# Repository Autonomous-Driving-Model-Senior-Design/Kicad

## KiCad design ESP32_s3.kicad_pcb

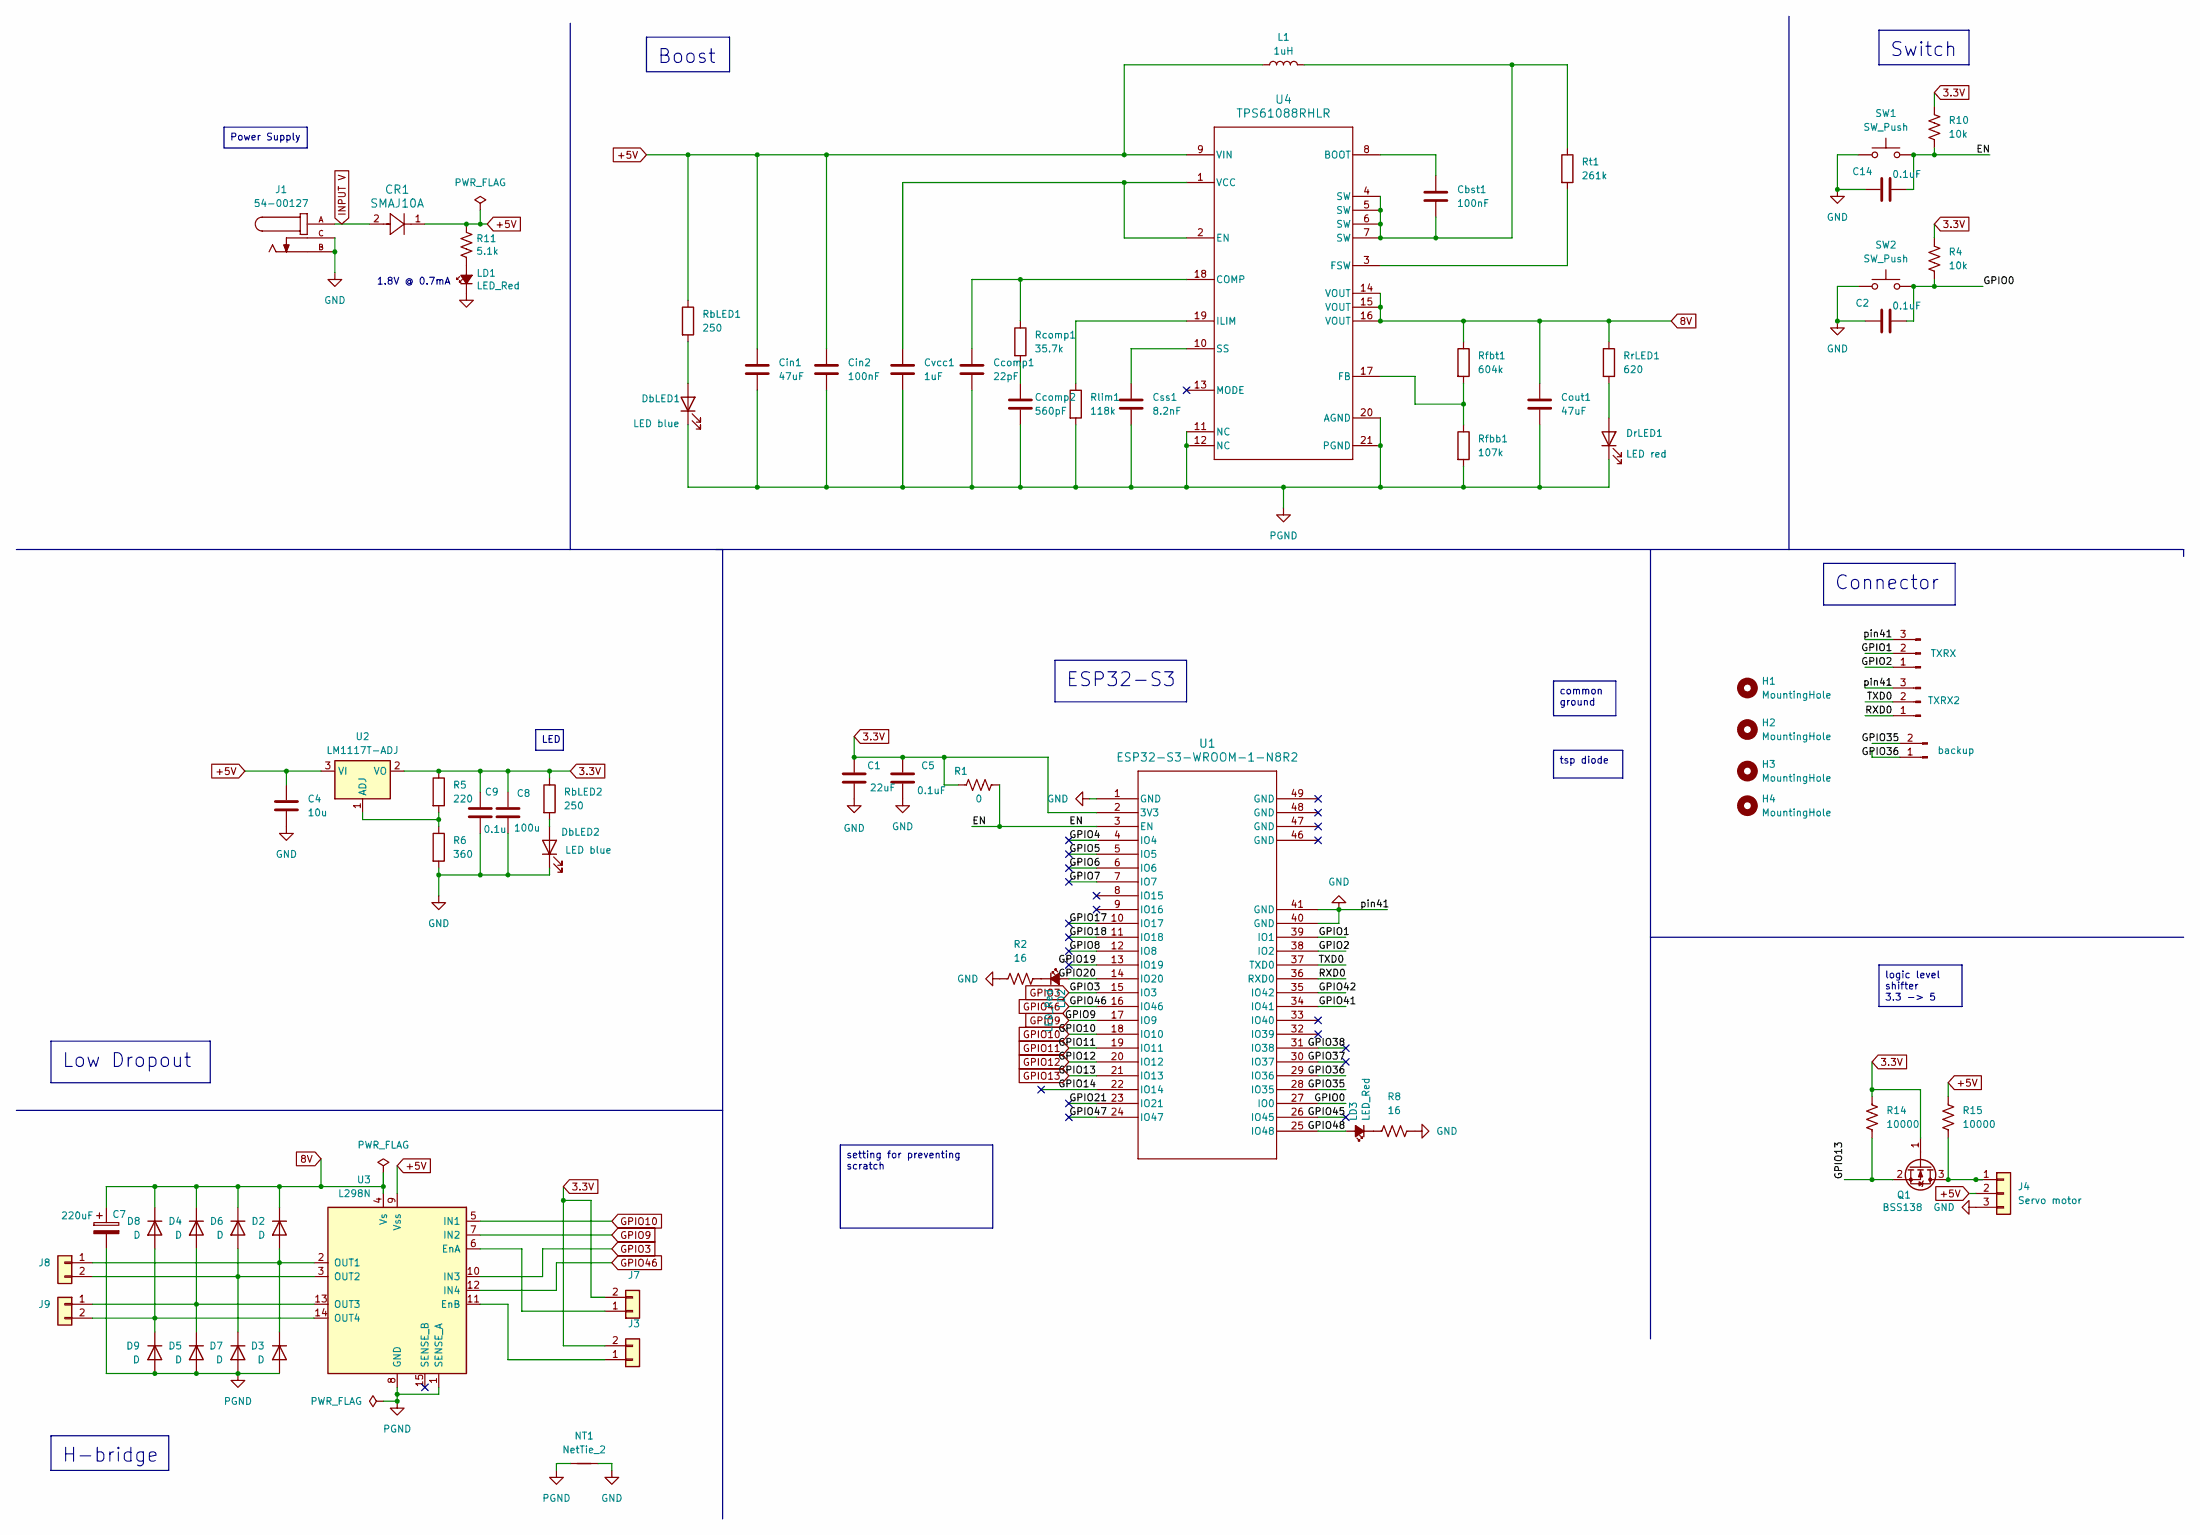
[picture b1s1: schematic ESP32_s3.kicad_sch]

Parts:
C1: 22uF; CAPC2012X135N
C2, C5, C14: 0.1uF; CAPC3316X140N
C4: 10u; CAPC230145_145N_KEM
C7: 220uF; CAPC3216X190N
C8: 100u; CAPC2012X145N
C9: 0.1u; CAPC2012X145N
CR1: SMAJ10A; SMASeries_LTF
Cbst1: 100nF; CAPC2012X94N
Ccomp1: 22pF; CAPC220145_90N_KEM
Ccomp2: 560pF; CAPC2012X88N
Cin1: 47uF; G-32_MUR
Cin2: 100nF; CAPC2012X94N
Cout1: 47uF; G-32_MUR
Css1: 8.2nF; CAPC2012X94N
Cvcc1: 1uF; cap_EMK212B7105KG-T_TAY
D2, D3, D4, D5, D6, D7, D8, D9: D; DO-41_STM
DbLED1, DbLED2: LED blue; WL-SMCW_0805
DrLED1: LED red; WL-SMCW_0805
H1, H2, H3, H4: MountingHole; MountingHole_2.7mm
J1: 54-00127; TENSILITY_54-00127; PARTREV A
J3, J7, J8, J9: Conn_01x02; CONN_61300211121_WRE
J4: Servo motor; 61300311121
J11: backup; CONN_61300211121_WRE
J14: TXRX; 61300311121
J15: TXRX2; 61300311121
L1: 1uH; IND_VLS6045EX-1R0N
LD1, LD2, LD3: LED_Red; LED_0805_2012Metric
NT1: NetTie_2; NetTie-2_SMD_Pad2.0mm
Q1: BSS138; SOT-23
R1: 0; RESC3216X70N
R2, R8: 16; RESC2012X65N
R4, R10: 10k; RESC2012X50N
R5: 220; RESC2012X65N
R6: 360; RESC2012X60N
R11: 5.1k; RESC2012X50N
R14, R15: 10000; RESC2012X50N
RbLED1, RbLED2: 250; RESC2012X50N
Rcomp1: 35.7k; RESC2012X50N
Rfbb1: 107k; RESC2012X50N
Rfbt1: 604k; RES_ERJ6ENF6043V
Rlim1: 118k; RESC2012X70N
RrLED1: 620; RESC2012X50N
Rt1: 261k; RESC2012X50N
SW1, SW2: SW_Push; SW_SPST_PTS645
U1: ESP32-S3-WROOM-1-N8R2; ESP32-S3-WROOM-1_EXP
U2: LM1117T-ADJ; TO254P1054X470X1955-3
U3: L298N; TO-220-15_P2.54x2.54mm_StaggerOdd_Lead4.58mm_Vertical
U4: TPS61088RHLR; IC_TPS61088RHLR

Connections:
3.3V: C1.1, C5.1, C8.1, C9.1, J3.2, J7.2, Q1.1 (G), R1.1, R4.2, R5.1, R10.2, R14.2, RbLED2.1, U1.2 (3V3), U2.2 (VO)
8V: C7.1, Cout1.1, D2.1 (K), D4.1 (K), D6.1 (K), D8.1 (K), Rfbt1.1, RrLED1.1, U3.4 (Vs), U4.14 (VOUT), U4.15 (VOUT), U4.16 (VOUT)
+5V: C4.1, CR1.1, Cin1.1, Cin2.1, J4.2, L1.1, R11.1, R15.2, RbLED1.1, U2.3 (VI), U3.9 (Vss), U4.9 (VIN)
/EN: C14.1, R1.2, R10.1, SW1.2, U1.3 (EN)
/GPIO0: C2.1, R4.1, SW2.2, U1.27 (IO0)
/GPIO1: J14.2, U1.39 (IO1)
/GPIO2: J14.1, U1.38 (IO2)
/GPIO4: U1.4 (IO4)
/GPIO5: U1.5 (IO5)
/GPIO6: U1.6 (IO6)
/GPIO7: U1.7 (IO7)
/GPIO8: U1.12 (IO8)
/GPIO14: U1.22 (IO14)
/GPIO17: U1.10 (IO17)
/GPIO18: U1.11 (IO18)
/GPIO19: U1.13 (IO19)
/GPIO20: LD2.2 (A), U1.14 (IO20)
/GPIO21: U1.23 (IO21)
/GPIO35: J11.2, U1.28 (IO35)
/GPIO36: J11.1, U1.29 (IO36)
/GPIO37: U1.30 (IO37)
/GPIO38: U1.31 (IO38)
/GPIO41: U1.34 (IO41)
/GPIO42: U1.35 (IO42)
/GPIO45: U1.26 (IO45)
/GPIO47: U1.24 (IO47)
/GPIO48: LD3.2 (A), U1.25 (IO48)
/RXD0: J15.1, U1.36 (RXD0)
/TXD0: J15.2, U1.37 (TXD0)
GPIO3: U1.15 (IO3), U3.10 (IN3)
GPIO9: U1.17 (IO9), U3.7 (IN2)
GPIO10: U1.18 (IO10), U3.5 (IN1)
GPIO11: U1.19 (IO11)
GPIO12: U1.20 (IO12)
GPIO13: Q1.2 (S), R14.1, U1.21 (IO13)
GPIO46: U1.16 (IO46), U3.12 (IN4)
INPUT V: CR1.2, J1.A
unnamed: Cbst1.2, L1.2, Rt1.1, U4.4 (SW), U4.5 (SW), U4.6 (SW), U4.7 (SW)
unnamed: Ccomp2.1, Rcomp1.2
unnamed: D2.2 (A), D3.1 (K), J8.1, U3.2 (OUT1)
unnamed: D4.2 (A), D5.1 (K), J9.1, U3.13 (OUT3)
unnamed: D6.2 (A), D7.1 (K), J8.2, U3.3 (OUT2)
unnamed: D8.2 (A), D9.1 (K), J9.2, U3.14 (OUT4)
unnamed: DbLED1.2 (A), RbLED1.2
unnamed: DbLED2.2 (A), RbLED2.2
unnamed: DrLED1.2 (A), RrLED1.2
unnamed: J3.1, U3.11 (EnB)
unnamed: J4.1, Q1.3 (D), R15.1
unnamed: J7.1, U3.6 (EnA)
unnamed: LD1.2 (A), R11.2
unnamed: LD3.1 (K), R8.1
unnamed: R5.2, R6.1, U2.1 (ADJ)
unnamed: Cbst1.1, U4.8 (BOOT)
unnamed: Ccomp1.1, Rcomp1.1, U4.18 (COMP)
unnamed: Cvcc1.1, U4.1 (VCC), U4.2 (EN)
unnamed: Rfbb1.1, Rfbt1.2, U4.17 (FB)
unnamed: Rt1.2, U4.3 (FSW)
unnamed: Rlim1.1, U4.19 (ILIM)
unnamed: Css1.1, U4.10 (SS)
PGND: C7.2, Ccomp1.2, Ccomp2.2, Cin1.2, Cin2.2, Cout1.2, Css1.2, Cvcc1.2, D3.2 (A), D5.2 (A), D7.2 (A), D9.2 (A), DbLED1.1 (K), DrLED1.1 (K), NT1.1, Rfbb1.2, Rlim1.2, U3.1 (SENSE_A), U3.8 (GND), U4.11 (NC), U4.12 (NC), U4.20 (AGND), U4.21 (PGND)

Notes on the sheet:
Low Dropout
Boost
H-bridge
logic level shifter 3.3 -> 5
Power Supply
Connector
tsp diode
setting for preventing scratch
common ground
Switch
LED
ESP32-S3
1.8V @ 0.7mA

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
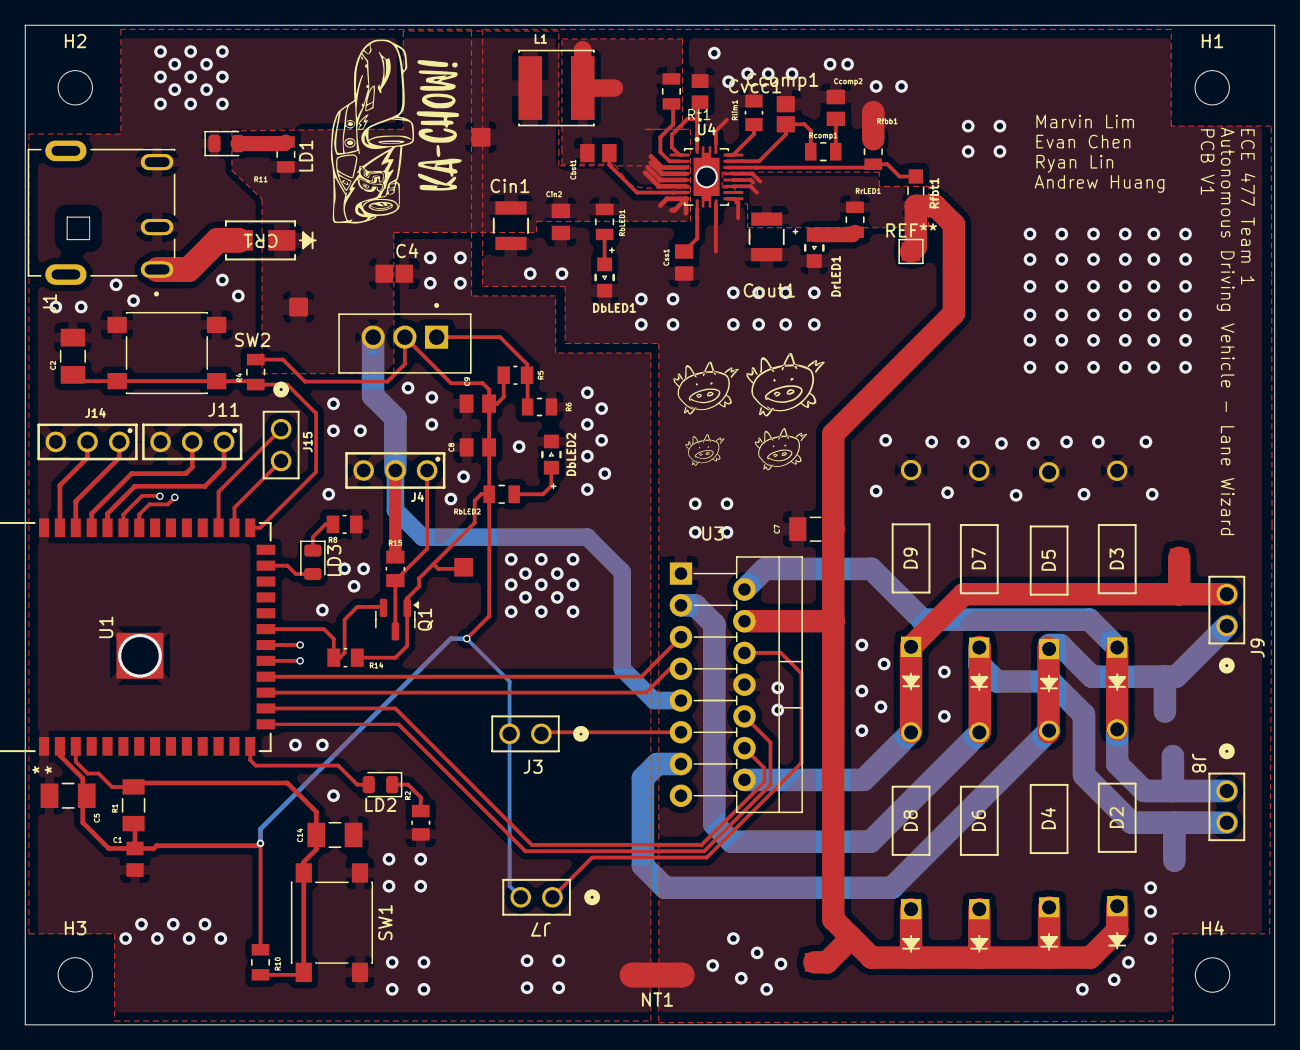
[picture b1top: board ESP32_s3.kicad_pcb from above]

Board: 2 copper layers, 100.0 x 80.0 mm, 71 parts (0 on the bottom side), 44 nets.

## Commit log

2024-10-03 add file
2024-10-03 Finished PCB Boost Layout
2024-10-03 PCB update
2024-10-03 added jetsonnano connector
2024-10-03 update micro PCB
2024-10-03 add resistors to debugging led
2024-10-03 update PCB layout
2024-10-04 PCB layout done (need traces)
2024-10-04 small fix of connector and LM1117 footprint
2024-10-04 complete PCB layout in region
2024-10-05 add a few traces
2024-10-05 update trace
2024-10-07 update traces
2024-10-07 update drill holes and name
2024-10-08 fix acute angles
2024-10-09 add pig
2024-10-09 fix error
2024-10-09 fix hbridge input voltage
2024-10-09 update schematic and PCB
2024-10-09 update labels and traces
2024-10-10 fix net label
2024-10-10 change layout
2024-10-10 change barrel jack
2024-10-10 footprint fix
2024-10-10 update schematic and layout
2024-10-11 update layout & mounting holes
2024-10-12 layout v1
2024-10-16 update PCB
2024-10-18 remove jetson power and fix acute angle
